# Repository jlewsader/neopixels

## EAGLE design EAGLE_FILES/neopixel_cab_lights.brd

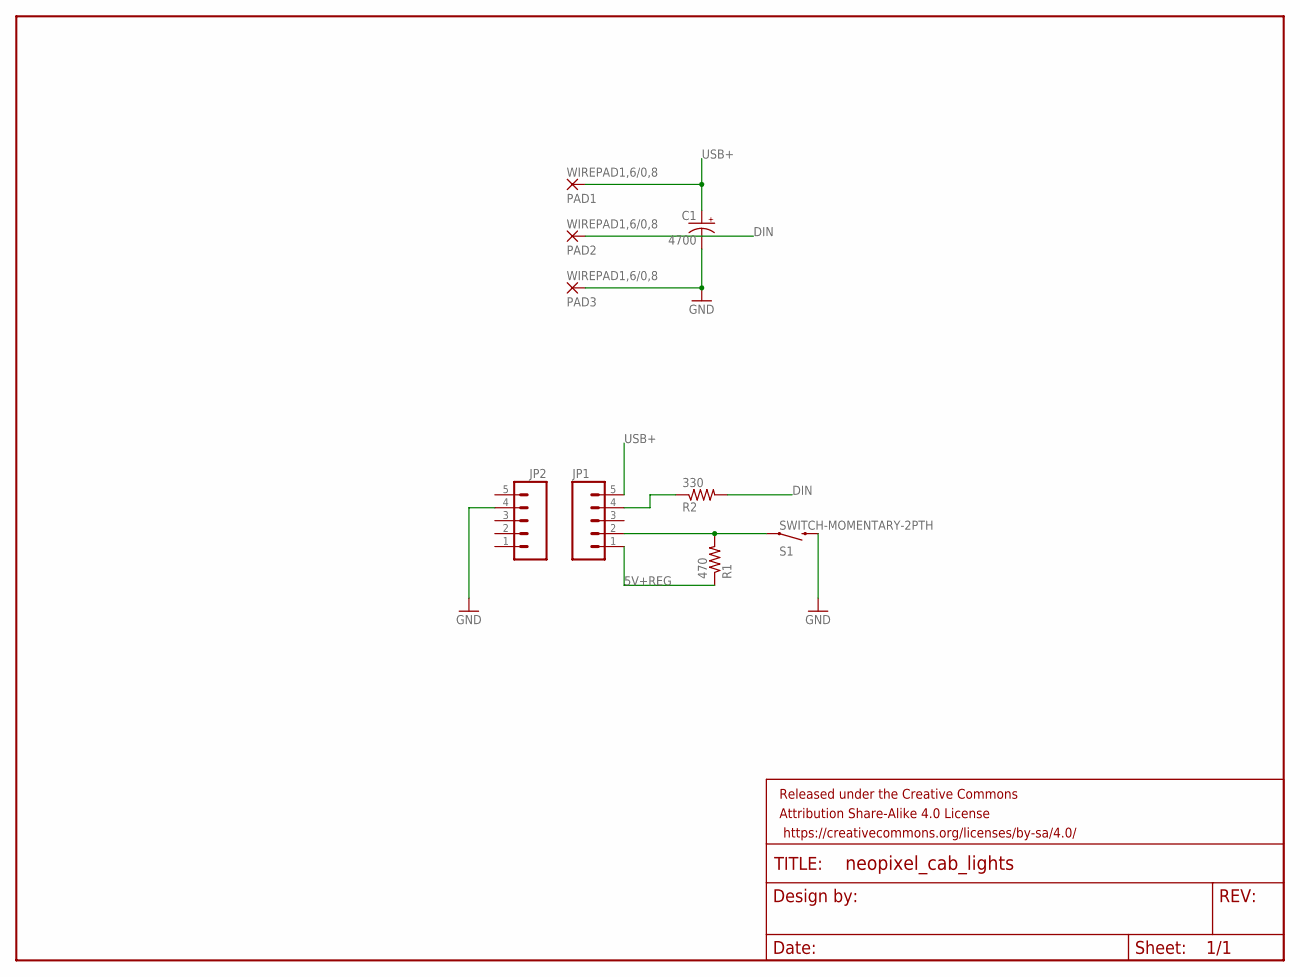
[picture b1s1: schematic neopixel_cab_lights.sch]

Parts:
C1: 4700; CPOL-RADIAL-100UF-25V
FRAME1: FRAME-LETTERNO_PACKAGE; DUMMY
JP1, JP2: M05PTH; 1X05
PAD1, PAD2, PAD3: WIREPAD1,6/0,8; 1,6/0,8
R1: 470; AXIAL-0.4
R2: 330; AXIAL-0.4
S1: SWITCH-MOMENTARY-2PTH; TACTILE-PTH

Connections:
5V+REG: JP1.1, R1.P$1 (1)
DIN: PAD2.1, R2.P$2 (2)
GND: C1.2 (-), JP2.4, PAD3.1, S1.3 (2)
unnamed: JP1.2, R1.P$2 (2), S1.1
unnamed: JP1.4, R2.P$1 (1)
USB+: C1.1 (+), JP1.5, PAD1.1

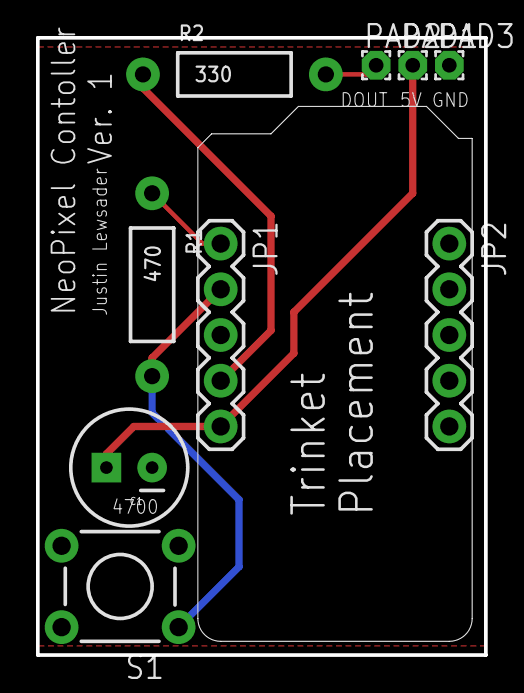
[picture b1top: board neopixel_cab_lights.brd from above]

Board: 2 copper layers, 24.9 x 34.3 mm, 10 parts (0 on the bottom side), 6 nets.

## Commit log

2015-11-29 working button, just have to hold through colorWipe or other long functions
2015-11-30 Starting Eagle & Fritzing files
2015-11-30 Eagle BRD & SCH files update.. Still working on board
2015-12-01 board finished
2015-12-01 restructure
2015-12-01 Add GERBER files
2015-12-05 change some timings in functions
2015-12-11 clean button code to make work better
2015-12-11 more lit thru whiteTwinkle func

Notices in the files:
parts and their libraries:
SparkFun-Capacitors: Licensing: Creative Commons ShareAlike 4.0 International - https://creativecommons.org/licenses/by-sa/4.0
SparkFun-Aesthetics: Released under the Creative Commons Attribution Share-Alike 4.0 License
SparkFun-Aesthetics: https://creativecommons.org/licenses/by-sa/4.0
